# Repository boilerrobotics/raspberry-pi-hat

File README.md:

# RaspberryPi-Hat

Please update this readme.
Please make a KiCAD project, then update the PROJECT_NAME at the top of the pcb_image.yaml (inside the .github/workflows folder)

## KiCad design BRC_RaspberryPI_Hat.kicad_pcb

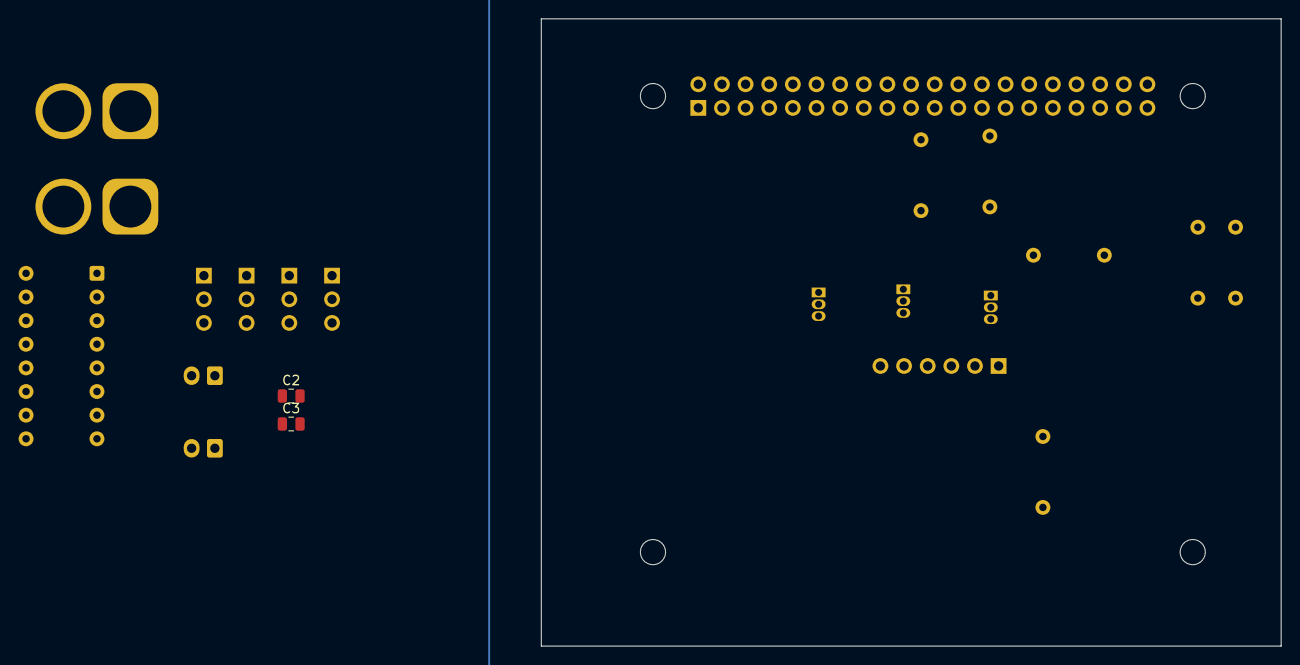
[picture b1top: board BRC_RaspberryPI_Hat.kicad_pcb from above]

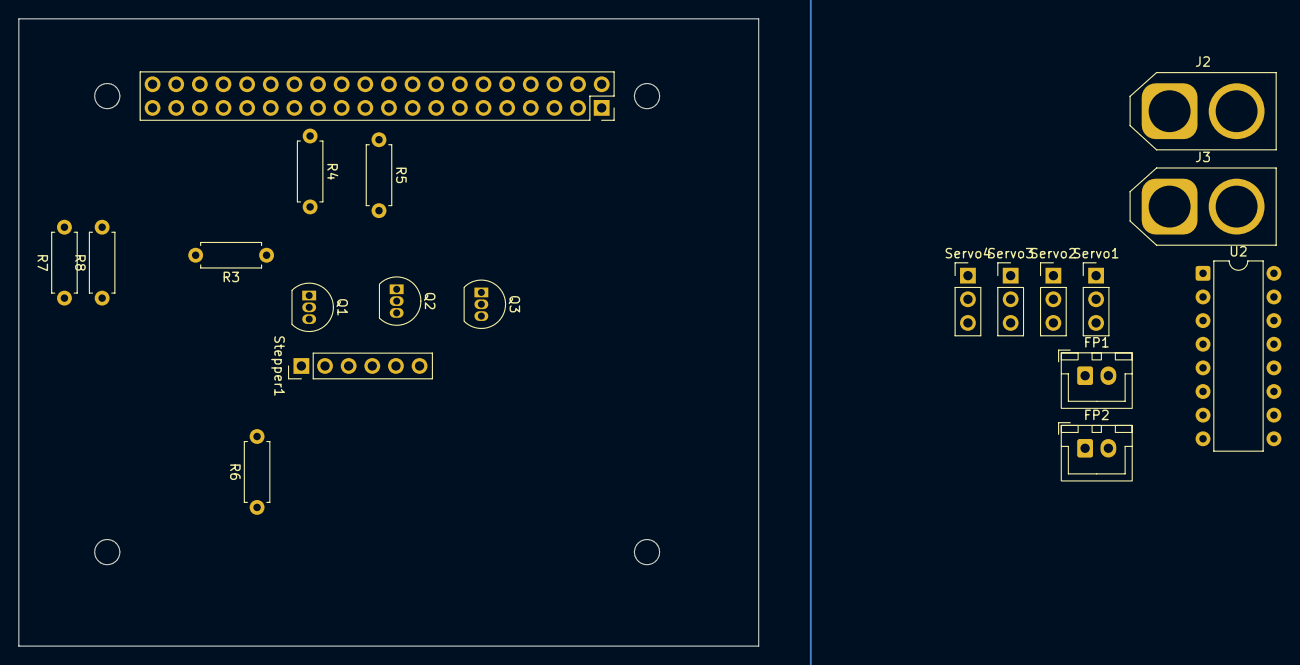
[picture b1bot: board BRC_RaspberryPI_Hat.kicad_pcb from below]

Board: 2 copper layers, 79.5 x 67.4 mm, 26 parts (20 on the bottom side), 27 nets.

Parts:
C2, C3: 10uF; C_0805_2012Metric
FP1, FP2: Conn_01x02; JST_XH_B2B-XH-A_1x02_P2.50mm_Vertical
J1: GPIO; PinSocket_2x20_P2.54mm_Vertical
J2, J3: Conn_01x02; AMASS_XT60-F_1x02_P7.20mm_Vertical
MH1, MH2, MH3, MH4: MountingHole_2.7mm_M2.5
Q1, Q2, Q3: PN2222A; TO-92_Inline
R3, R6, R7: 10k; R_Axial_DIN0207_L6.3mm_D2.5mm_P7.62mm_Horizontal
R4, R5, R8: 1k; R_Axial_DIN0207_L6.3mm_D2.5mm_P7.62mm_Horizontal
Servo1, Servo2, Servo3, Servo4: Conn_01x03; PinHeader_1x03_P2.54mm_Vertical
Stepper1: Conn_01x06; PinHeader_1x06_P2.54mm_Vertical
U2: SN754410NE; DIP-16_W7.62mm

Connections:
+3V3: J1.1, J1.17
+5V: C2.2, J1.2, J1.4, J2.1, Servo1.2, Servo2.2, Servo3.2, Servo4.2, Stepper1.1, Stepper1.3, Stepper1.5, U2.16 (VCC1)
+12V: C3.2, J3.1, U2.8 (VCC2)
/GPIO5: J1.29, U2.9 (3,4EN)
/GPIO6: J1.31, U2.10 (3A)
/GPIO17: J1.11, U2.1 (1,2EN)
/GPIO22: J1.15, U2.2 (1A)
/GPIO23: J1.16, R4.1
/GPIO24: J1.18, R5.1
/GPIO25: J1.22, R8.1
/GPIO26: J1.37, U2.15 (4A)
/GPIO27: J1.13, U2.7 (2A)
/SERVO1_PWM: J1.32, Servo1.3
/SERVO2_PWM: J1.33, Servo2.3
/SERVO3_PWM: J1.12, Servo3.3
/SERVO4_PWM: J1.35, Servo4.3
GND: C2.1, C3.1, J1.6, J1.9, J1.14, J1.20, J1.25, J1.30, J1.34, J1.39, J2.2, J3.2, Q1.1 (E), Q2.1 (E), Q3.1 (E), R3.2, R6.2, R7.2, Servo1.1, Servo2.1, Servo3.1, Servo4.1, U2.4 (GND), U2.5 (GND), U2.12 (GND), U2.13 (GND)
unnamed: FP1.1, U2.3 (1Y)
unnamed: FP1.2, U2.6 (2Y)
unnamed: FP2.1, U2.11 (3Y)
unnamed: FP2.2, U2.14 (4Y)
unnamed: Q1.2 (B), R3.1, R4.2
unnamed: Q1.3 (C), Stepper1.2
unnamed: Q2.2 (B), R5.2, R6.1
unnamed: Q2.3 (C), Stepper1.4
unnamed: Q3.2 (B), R7.1, R8.2
unnamed: Q3.3 (C), Stepper1.6
